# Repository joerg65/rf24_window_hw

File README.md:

# rf24_window_hw  

This is the KiCad project of RF24 Window Sensor.

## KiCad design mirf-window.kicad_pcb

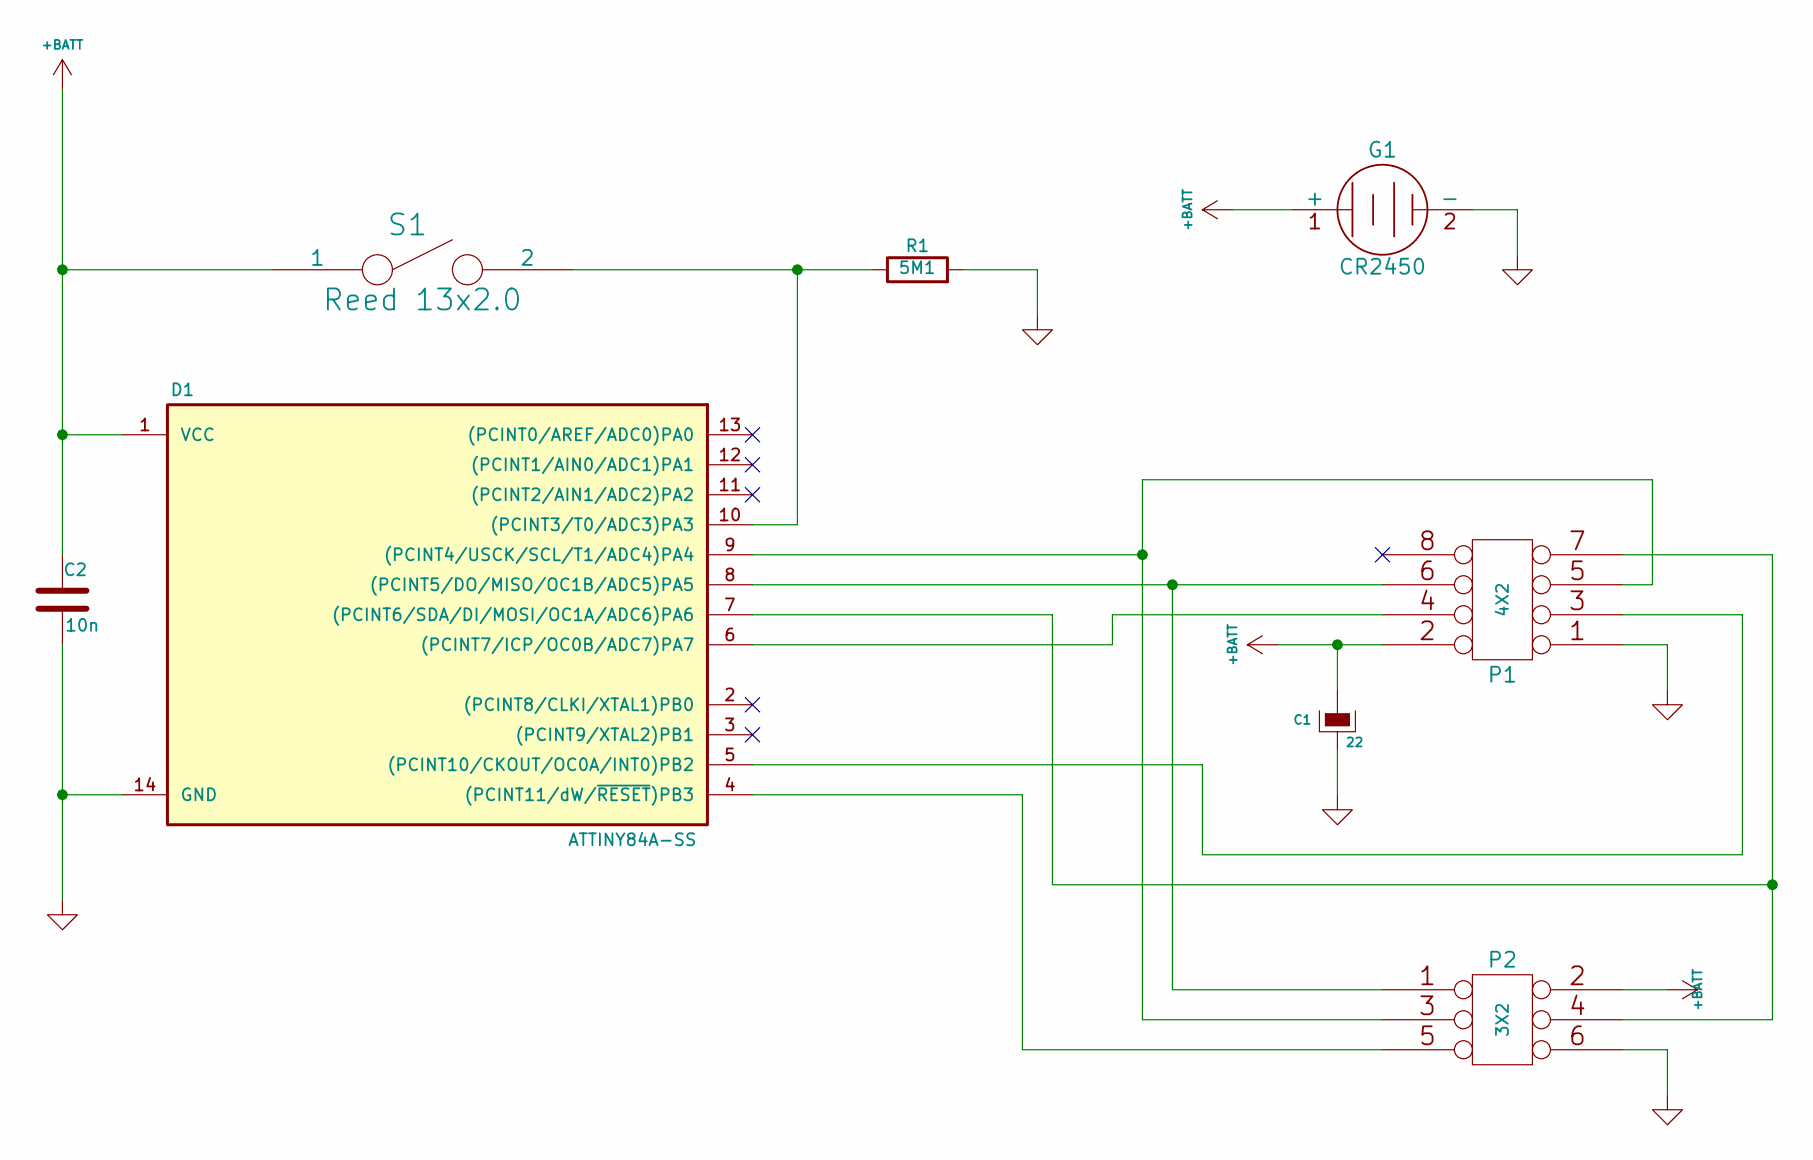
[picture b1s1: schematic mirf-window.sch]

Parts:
C1: 22
C2: 10n; C_1206_HandSoldering
D1: ATTINY84A-SS; SSOP-14
G1: CR2450; SUPER_CAP
P1: 4X2; Pin_Header_Straight_2x04
P2: 3X2; Pin_Header_Straight_2x03
R1: 5M1
S1: Reed 13x2.0

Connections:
+BATT: C1.1, C2.1, D1.1 (VCC), G1.1 (+), P1.2, P2.2, S1.1
GND: C1.2, C2.2, D1.14 (GND), G1.2 (-), P1.1, P2.6, R1.2
unnamed: D1.4 ((PCINT11/dW/~RESET~)PB3), P2.5
unnamed: D1.5 ((PCINT10/CKOUT/OC0A/INT0)PB2), P1.3
unnamed: D1.6 ((PCINT7/ICP/OC0B/ADC7)PA7), P1.4
unnamed: D1.7 ((PCINT6/SDA/DI/MOSI/OC1A/ADC6)PA6), P1.7, P2.4
unnamed: D1.8 ((PCINT5/DO/MISO/OC1B/ADC5)PA5), P1.6, P2.1
unnamed: D1.9 ((PCINT4/USCK/SCL/T1/ADC4)PA4), P1.5, P2.3
unnamed: D1.10 ((PCINT3/T0/ADC3)PA3), R1.1, S1.2

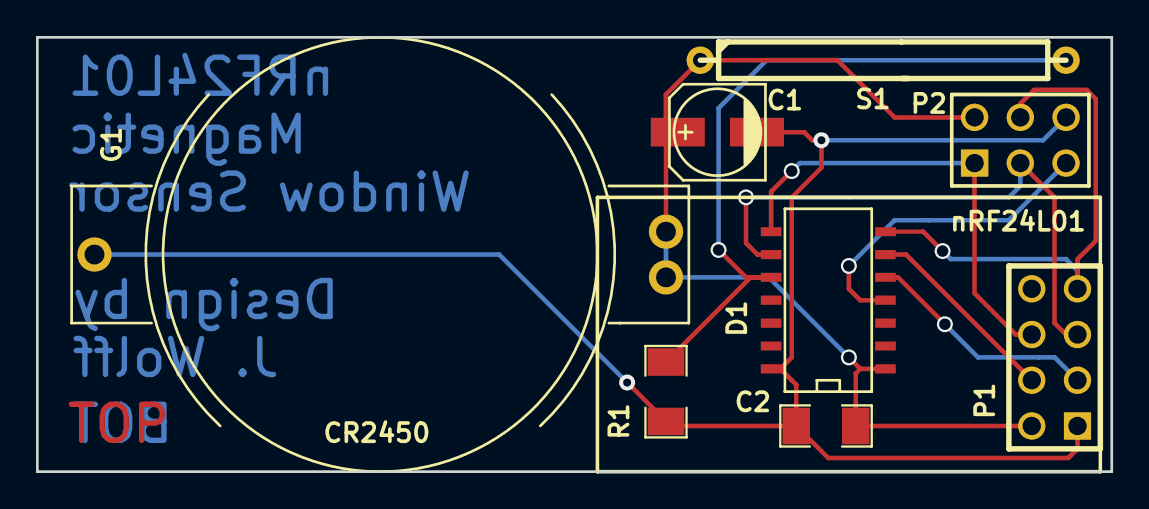
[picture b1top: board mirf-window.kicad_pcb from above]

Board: 2 copper layers, 59.7 x 24.1 mm, 8 parts (0 on the bottom side), 9 nets.
